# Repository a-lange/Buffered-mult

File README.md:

This is a buffered mult, made in Kicad for 8HP format. 

It is tested, and works.

For now there is a few minor issues:
- power connector is too close to the edge, so it overhangs a tiny bit. So use an unkeyed pin-header and note that -12v(red stripe) is towards the edge of the board.
- GND is missing on the top jacks, easily patched manually.

The front panel is reversible, the back has a simpler layout with no logo, text or copier.

Use it however you like.

The text says 'copier' in Norwegian, and the creature on the bottom is the friendly "ullmann"(wool-man).

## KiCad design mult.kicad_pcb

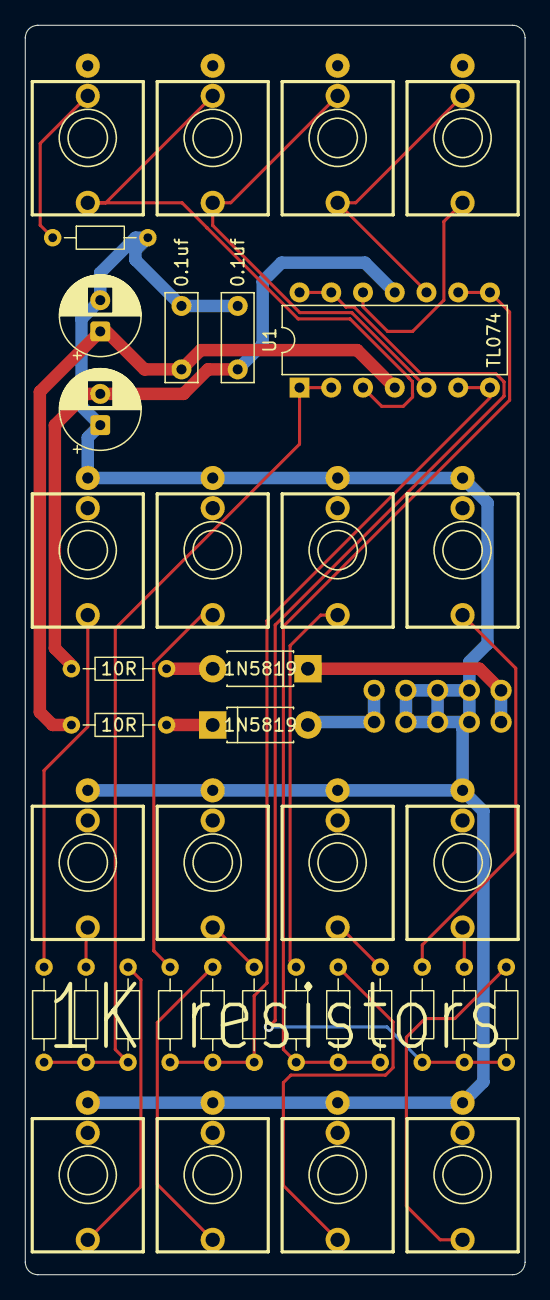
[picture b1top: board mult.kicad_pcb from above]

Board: 2 copper layers, 40.0 x 100.0 mm, 39 parts (1 on the bottom side), 28 nets.

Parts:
C1, C3: 10uF; CP_Radial_D6.3mm_P2.50mm
C2, C4: 0.1uf; C_Disc_P5.08mm
D1, D2: 1N5819; D_DO-41_P7.62mm_Horizontal
J1, J2, J3, J4, J5, J6, J7, J8, J9, J10, J11, J12, J13, J14, J15, J16: EighthInch_PJ398SM
J17: Eurorack_Power_10pin_Unshrouded; Pins_2x05_2.54mm_TH
R1, R2, R3, R4, R5, R6, R7, R8, R9, R10, R11, R12: 1k; R_Axial_DIN0204_L3.6mm_D1.6mm_P7.62mm_Horizontal
R13: 1M; R_Axial_DIN0204_L3.6mm_D1.6mm_P7.62mm_Horizontal
R15, R16: 10R; R_Axial_DIN0204_L3.6mm_D1.6mm_P7.62mm_Horizontal
U1: TL074; DIP-14_W7.62mm

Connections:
+12v: C1.1, C2.2, R15.2, U1.4 (V+)
-12v: C3.2, C4.1, R16.2, U1.11 (V-)
GND: C1.2, C2.1, C3.1, C4.2, J5.2 (SHEILD), J6.2 (SHEILD), J7.2 (SHEILD), J8.2 (SHEILD), J9.2 (SHEILD), J10.2 (SHEILD), J11.2 (SHEILD), J12.2 (SHEILD), J13.2 (SHEILD), J14.2 (SHEILD), J15.2 (SHEILD), J16.2 (SHEILD), J17.3 (GND), J17.4 (GND), J17.5 (GND), J17.6 (GND), J17.7 (GND), J17.8 (GND), R13.2 (-)
unnamed: D1.2 (A), J17.1 (+12V), J17.2 (+12V)
unnamed: D1.1 (K), R15.1
unnamed: D2.2 (A), R16.1
unnamed: D2.1 (K), J17.9 (-12V), J17.10 (-12V)
unnamed: J1.1 (SIG), J2.3 (SW), U1.3 (+)
unnamed: J1.3 (SW), R13.1 (+)
unnamed: J2.1 (SIG), J3.3 (SW), U1.5 (+)
unnamed: J3.1 (SIG), J4.3 (SW), U1.10 (+)
unnamed: J4.1 (SIG), U1.12 (+)
unnamed: J5.1 (SIG), R1.2 (-)
unnamed: J6.1 (SIG), R2.2 (-)
unnamed: J7.1 (SIG), R3.2 (-)
unnamed: J8.1 (SIG), R4.2 (-)
unnamed: J9.1 (SIG), R6.2 (-)
unnamed: J10.1 (SIG), R5.2 (-)
unnamed: J11.1 (SIG), R7.2 (-)
unnamed: J12.1 (SIG), R8.2 (-)
unnamed: J13.1 (SIG), R9.2 (-)
unnamed: J14.1 (SIG), R10.2 (-)
unnamed: J15.1 (SIG), R11.2 (-)
unnamed: J16.1 (SIG), R12.2 (-)
unnamed: R1.1 (+), R2.1 (+), R3.1 (+), U1.1, U1.2 (-)
unnamed: R4.1 (+), R5.1 (+), R6.1 (+), U1.6 (-), U1.7
unnamed: R7.1 (+), R8.1 (+), R9.1 (+), U1.8, U1.9 (-)
unnamed: R10.1 (+), R11.1 (+), R12.1 (+), U1.13 (-), U1.14

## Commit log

2026-03-09 Update README.md
    tested
